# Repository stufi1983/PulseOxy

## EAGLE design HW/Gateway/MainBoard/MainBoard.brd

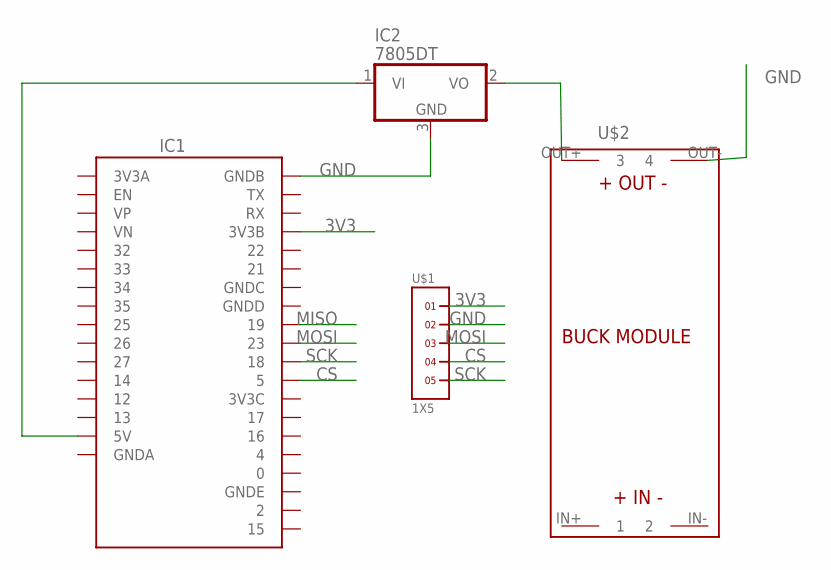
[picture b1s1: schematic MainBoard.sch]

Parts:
IC1: SSFD_LOLIN32_WEMOS_CHINA_W_BATT
IC2: 7805DT; TO252
U$1: 1X5
U$2: BUCK_MODULE; BUCK_MODULE_SMALL

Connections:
3V3: IC1.3V3B, U$1.1
CS: IC1.5, U$1.4
GND: IC1.GNDB, IC2.3 (GND), U$1.2, U$2.OUT- (4)
MISO: IC1.19
MOSI: IC1.23, U$1.3
unnamed: IC1.5V, IC2.1 (VI)
unnamed: IC2.2 (VO), U$2.OUT+ (3)
SCK: IC1.18, U$1.5

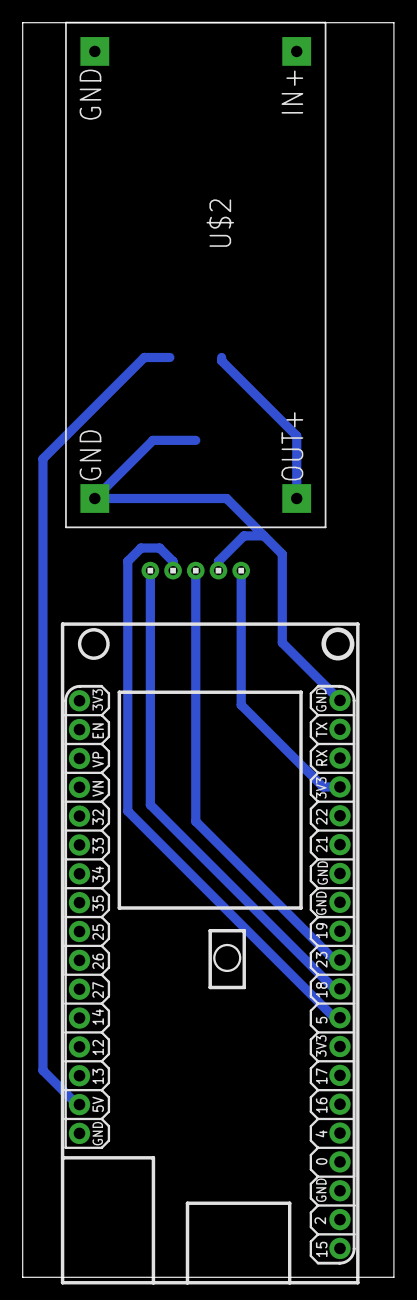
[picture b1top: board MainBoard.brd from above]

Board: 2 copper layers, 32.7 x 110.5 mm, 4 parts (1 on the bottom side), 7 nets.

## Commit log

2022-09-07 Add PCB
2024-08-23 ketemu
2024-08-23 reconect masih failed
2024-08-24 beres kari tampilan
2024-08-25 wis ok, reconnect pakai reset
2024-08-25 heart rate by notif
2024-08-25 display in oled
2024-08-25 ADD WDT
2024-08-26 tinggal displsy
2024-08-28 finishing
2024-08-28 json
2024-08-28 send json ok
2024-08-31 website
2024-09-02 Release
2024-09-02 web release
